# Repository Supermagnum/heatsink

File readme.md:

# DIY Liquid Cooling Suit

Those are cooling suits, used in the lowest layer on space suits.
It has hoses for circulation of cooling medium. 
A single layer of fabric may be used, with the tubing either on the inside directly contacting the wearer's skin, or on the outside separated by the fabric. If two layers of fabric are used, stitched channels can be formed which enclose the tubing between the two fabric layers. Where flame resistance is needed, the garment may be constructed out of materials such as nomex. 
If anyone has seen the apollo 13 movie, the boxes carried by the astronauts on the way to the space capsule is a heat exchanger that provides cooling until the suits can be hooked up to the capsules internal cooling system.
That box also provides O2.

I think that NASA just used ice, battery and a pump in those boxes, and you need the capacity to at least transport 200W because the human body generates about 100W. One could rip out the heat exchanger from a car, the bit who heats air, make the suit out of spandex and sew in loops. Mesh cloth or mesh garments are also suitable. 
A radiator for a CPU liquid cooler should be ideal. Hook that up to a aquarium pump or similar, and the heat exchanger/radiator that goes in a bucket of ice cubes or phase shifting material and water. The pump will need to be able to flow around 4 liters per minute, and must run on 12V and accept PWM control.

The cooling loop is made of 
6 pvc hoses in parallel, measuring 6 mm ØID x 9 mm ØOD, length 4 meters per hose. Total internal surface of the hoses is 4524.7 cm². External surface 6789.6 cm2. The heat exchanger as well as hoses and pump contain 3 liters of inhibited propylene glycol and water mix (25–30%). Brass or metal connectors, hose barbs, and hose clamps should be used. Two manifolds are required — one for liquid distribution and one for collection — built from T-pieces, elbows, and other fittings (see [Coolant plumbing](#coolant-plumbing) below).

## Table of contents

- [Thermal Calculations](#thermal-calculations)
  - [Cooling 3 liters from 40°C to 18°C](#cooling-3-liters-of-waterglycol-from-40c-to-18c-in-150-seconds)
  - [Ice as a cooling medium](#ice-as-a-cooling-medium)
  - [Maintaining 18°C coolant temperature](#maintaining-18c-coolant-temperature)
  - [Liquid-to-ice heat exchanger](#liquid-to-ice-heat-exchanger)
- [Phase-Change Materials](#phase-change-materials)
- [Temperature Control](#temperature-control)
  - [Coolant options](#coolant-options)
  - [Preliminary Arduino Firmware](#preliminary-arduino-firmware)
- [Required Hardware](#required-hardware)
- [Electronics component list](component-list.md)
  - [Assembly instructions](component-list.md#assembly-instructions)
  - [Board placement guide (arduino-shield.jpg)](component-list.md#board-placement-guide)
  - [Ordering the PCB from Gerber files](component-list.md#ordering-the-pcb-from-gerber-files)
  - [Soldering and wire splicing](component-list.md#soldering-and-wire-splicing)
  - [How to solder (NASA reference)](component-list.md#how-to-solder)
  - [How to splice wire properly](component-list.md#how-to-splice-wire-properly)
  - [Heat-shrink on splices](component-list.md#heat-shrink-on-splices)
- [Wiring Diagram](#wiring-diagram)
- [12V Power Setup](#12v-power-setup)
  - [12V DC safety and dry locations](#12v-dc-safety-and-dry-locations)
- [Container Setup](#container-setup)
- [Suit Fabric](#suit-fabric)
- [Coolant plumbing](#coolant-plumbing)
- [Pump Selection](#pump-selection)

---

## Thermal Calculations

### Cooling 3 liters of water/glycol from 40°C to 18°C in 150 seconds

How much heat must be removed:

Q = mc∆T  
m = 3 kg  
Specific heat capacity of water = 4.18 J/g°C  
Temperature change: 40 - 18 = 22°C

Q = 3 kg × 4180 J/kg°C × 22°C = **275,880 J**

This means the heat exchanger removes 275,880 joules of heat from the cooling loop in 150 seconds.

To convert joules into watts: Joules / time in seconds = **~1,848W** during initial cooldown.

---

### Ice as a cooling medium

To remove 1848.8 watts of energy from 3 liters of water at 40°C over 150 seconds:

Q = P × t = 1848.8 W × 150 s = **277,320 J**

Mass of water being cooled:

m = Q / (c × ΔT) = 277320 / (4.18 × 40) ≈ **1.658 kg**

So approximately 1.65 kilograms of ice would be needed for the initial cooldown phase.

It will take approximately 42.86 seconds to remove 275,880 joules of heat with a flow rate of 5 liters per minute.

---

### Maintaining 18°C coolant temperature

With ambient air temperature at 40°C:

ΔT_initial = 40°C - 18°C = 22°C

m_ice = (m × c × ΔT_initial) / L_f  
m_ice = (3 kg × 4186 J/kg°C × 22°C) / 334,000 J/kg ≈ **0.827 kg per hour**

Including 100W body heat: approximately **~2 kg of ice per hour** is needed.  
Flow rate for maintenance: **~2.5 liters per minute**.

---

### Liquid-to-ice heat exchanger

To extract 275,880 J of heat from ice over 150 seconds using 10mm OD / 0.8mm wall copper tube with a ΔT of 40°C and convective heat transfer coefficient of 200 W/m²·K:

Required copper tube length: approximately **7.32 meters**  
Inner surface: 1.848 m²  
Outer surface: 2.198 m²

---

## Phase-Change Materials

I suggest using Cold Gel Packs, Campingaz or similar brand as they reportedly last longer than ice cubes.

You can make something similar yourself:  
https://m.youtube.com/watch?v=Nqxjfp4Gi0k

- Heat capacity of the salt/water mixture: approximately **5,451.5 J/°C**
- Latent heat: approximately **3.39 J/g°C**
- Total weight of mixture: **1,695 grams**
- Be aware that it might expand slightly when frozen.
- Heat capacity of 1,695 grams of water ice: approximately **3,543.55 J/°C**

Also look at:  
https://www.cryopak.com/solutions/refrigerants/phase-change-materials/phase-5/

- Heat capacity of 2 kg mixture: approximately **6,432.92 J/°C**
- Heat capacity of 2 kg water ice: **4,180 J/°C**
- 2 kg of the mixture will last approximately **3 hours** — much better than water ice.

---

## Temperature Control

To keep coolant at 18°C (0°C coolant is uncomfortable and risks hypothermia):

Use an automotive NTC temperature sensor and an Arduino to control temperature. Sensor datasheet: [Bosch M12 NTC temperature sensor (PDF)](https://www.bosch-motorsport.com/content/downloads/Raceparts/Resources/pdf/Data%20sheet_70101387_Temperature_Sensor_NTC_M12.pdf)

Arduino shield schematic: [arduino-shield.pdf](arduino-shield/arduino-shield.pdf) ([shield project folder](arduino-shield/))

Mount the Bosch M12 NTC in the **collection manifold** (return side), as close to the suit as possible — **not in the ice container**. This measures warm coolant leaving the suit for pump control. Use PWM to regulate pump speed from that reading.

Why **inhibited propylene glycol** and water? The ice bath and phase-change blocks can drive slush **below 0°C** at the heat exchanger. A **25–30% PG mix** keeps the loop liquid while staying thin enough to pump through 6 mm hoses. Unlike ethylene glycol antifreeze, propylene glycol is **biodegradable and low-toxicity** — a better fit near a wearable loop (still not for drinking). Use secure hose barbs and clamps, pressure-test the loop, and increase PG percentage only if slush goes colder than your mix rating.

### Coolant options

#### Recommended — inhibited propylene glycol + water (25–30% mix)

**Best balance of cost, safety, and compatibility for this build.**

| Property | Detail |
| --- | --- |
| **Toxicity** | Non-toxic, food-grade safe. Used in RVs, food processing, and HVAC. Unlike ethylene glycol, PG is biodegradable and presents a much lower hazard to people and animals if spilled. |
| **Hose / seal compatibility** | Compatible with typical cooling-system plastics and elastomers — PVC hose, pump seals, and brass barbs used in this project. |
| **Freeze point** | ~**−10°C at 25%** PG — enough margin for light sub-zero slush without the extra viscosity and pumping cost of a 50% mix. Use **30%** if you need more headroom. |
| **Electrical** | **Not dielectric** — conductivity is typically **>2,000 µS/cm** (water-based, conductive). Fine for a pumped hose loop; do not use near bare electronics expecting insulation. |
| **Cost / availability** | Cheapest practical option. Sold as pre-mixed **inhibited** PG antifreeze under names such as **DOWFROST**, **AMSOIL ANT**, **Cryo-Tek**, or generic **RV / marine antifreeze** at hardware and auto stores. Confirm the label says **propylene glycol**, not ethylene glycol. |

Mix with **distilled water** if buying full-strength concentrate; follow the label for your target freeze point.

#### Optional — ElectroCool and similar synthetic fluids

**ElectroCool** (Engineered Fluids) and similar **dielectric** immersion coolants are non-conductive and wash off with soap and water, but they are **much more expensive** and designed for electronics immersion — not as a default for this PVC-hose suit loop. Only consider if you validate compatibility with every hose, pump seal, and fitting, and accept the higher fluid cost.

#### Other alternatives

| Fluid | Notes |
| --- | --- |
| **USP / food-grade PG + water (DIY mix)** | Same family as above; buy PG concentrate and mix yourself. Lowest unit cost. |
| **Glycerol (glycerin) + water** | Non-toxic and biodegradable. Higher viscosity — may reduce flow in 6 mm hoses; weaker freeze protection per percent than PG. |
| **Potassium acetate / formate HTF** | Used in some commercial low-toxicity antifreeze systems. Verify pump, hose, and brass compatibility before use. |

#### Not recommended for a wearable loop

- **Ethylene glycol** (standard automotive antifreeze) — effective antifreeze but **acutely toxic**
- **Legacy PFAS / fluorinated fluids** — environmental persistence and regulatory phase-out
- **Plain water** — inadequate when slush goes below 0°C at the heat exchanger

#### Fill and service

- Use **distilled water** for mixing; tap water minerals cause scale and biofilm
- Pressure-test after fill; monitor for leaks on first runs (see [Coolant plumbing](#coolant-plumbing))
- Label the container and suit loop as containing glycol — not potable

### Preliminary Arduino Firmware

Two **momentary** switches adjust coolant temperature between 15°C and 25°C in 5°C steps (up/down).  
A **maintained toggle** switch on D4 enables manual pump override (full PWM on D9); off returns to automatic temperature control.  
Outputs on the [Arduino shield](arduino-shield/arduino-shield.pdf):
- **D9 → Q1 (TIP120):** pump PWM (temperature-controlled, or manual override via D4)
- **D7:** buzzer — out-of-ice alarm (>30°C for 2 minutes)
- **D8 → Q2 (TIP120):** spare 12V output (not used in current firmware)

LCD shows: target temperature, sensed temperature, current pump PWM.

Firmware repository:  
https://github.com/Supermagnum/heatsink/tree/main/firmware

---

## Required Hardware

1. **Arduino Uno R3** — bottom of the stack; see [component list](component-list.md)
2. [Heatsink control shield](arduino-shield/arduino-shield.pdf) — stacks on the Uno; [placement diagram](arduino-shield/arduino-shield.jpg) shows part positions, diode direction, and **+** wire marks. Order bare PCBs from [`arduino-shield/gerbers/`](arduino-shield/gerbers/) ([how to submit Gerbers](component-list.md#ordering-the-pcb-from-gerber-files)), then follow [assembly instructions](component-list.md#assembly-instructions). New to soldering? **20 W iron** and NASA/splice guides in [component list — Soldering and wire splicing](component-list.md#soldering-and-wire-splicing)
3. **LCD shield, 20×4, no buttons** — HD44780 display-only shield on top of the stack (not an LCD Keypad Shield)
4. NTC thermistor, [Bosch M12](https://www.bosch-motorsport.com/content/downloads/Raceparts/Resources/pdf/Data%20sheet_70101387_Temperature_Sensor_NTC_M12.pdf) (see [Coolant plumbing](#coolant-plumbing) for mounting)
5. **R1** — **MFP50SBBE52-50K** (50 kΩ, 0.1%) — DigiKey **MFP50SBBE52-50K-ND**
6. **D1–D3** — three **1N5407RL** flyback diodes — DigiKey **1N5407RL-ND** (or **1N5407RLG-ND** if unavailable)
7. **2× M3 nylon bolt and nut** — mount **Q1** and **Q2** tabs only; **no metal** hardware (12 V)
8. Shield stacking headers — DigiKey **1528-1074-ND** (Adafruit #85), one kit per bare control shield for Uno/LCD stack ([full DigiKey list](component-list.md#digikey-quick-order-bare-shield-populate))
9. Three **panel switches** on **SW1–SW3** (1×3 headers): two **100SP4T1B2M2QE** momentary (temp up/down), one **ANT13SECQE** maintained toggle (pump manual/auto). **Switch guards** (100SP / ANT compatible) recommended to prevent accidental actuation — especially on SW3
10. 12V submersible pump (4–5 L/min) — switched by **Q1 TIP120 on D9** on the control shield (max **5A**)
11. Optional: **5A inline fuses** on each 12V power cable branch (see [12V Power Setup](#12v-power-setup))
12. Crimped leads / screw terminals for panel switches, NTC, and 12 V — see [component list](component-list.md)
13. Hose clamps
14. Assorted T-pieces, elbows, connectors, adapters, and tube barbs (metal or PETG — see [Coolant plumbing](#coolant-plumbing))
15. Inhibited propylene glycol antifreeze (propylene, not ethylene) for 25–30% coolant mix
16. Liquid gasket or PTFE thread tape for sealed joints
17. Optional: small valves to control "zones"

### Arduino stack and connections

**Stack (bottom → top):** Arduino Uno R3 → heatsink control shield → **LCD shield without buttons**. Panel switches and NTC connect to the control shield headers/terminals only.

- Bosch M12 NTC (TH1) and 50K resistor (R1) form a voltage divider on A0; AREF feeds the divider top and sets the ADC reference
- **LCD shield** (20×4, HD44780, **no keypad**) on D12, D11, D10, D6, D5, D13 — see [Wiring Diagram](#wiring-diagram)
- Switches wired **pin → switch → GND** (active when grounded); firmware enables internal pull-ups on D2, D3, and D4
- **D2 / D3:** momentary — one temperature step per actuation
- **D4:** maintained toggle — ON = manual pump override, OFF = automatic
- D9 PWM drives **Q1 TIP120** on the shield — low-side switch for the pump (up to 5A)
- D7 drives the **buzzer** alarm output
- D8 drives **Q2 TIP120** for the spare 12V output
- Q1 and Q2 are TO-220 packages clamped to **built-in copper thermal zones** with **M3 nylon bolt and nut** each — **no metal mounting hardware** (12 V on the tab). **No add-on heatsinks**; the PCB spreads heat from the transistor tabs

---

## Wiring Diagram

Signal and power connections for the [Arduino shield](arduino-shield/arduino-shield.pdf). Ground all 12V loads to a common bus.

```mermaid
graph TD
    PSU["12V PSU / Battery"]

    PSU -->|12V| ARD["Arduino Uno\n+ control shield"]
    PSU -->|12V| Q1["TIP120 Q1\npump D9"]
    PSU -->|12V| Q2["TIP120 Q2\nspare D8"]

    ARD -->|D9 PWM| Q1
    Q1 --> PUMP["Submersible pump\n4–5 L/min"]

    ARD -->|D7| BUZ["Buzzer\nout-of-ice alarm"]
    ARD -->|D8| Q2
    Q2 --> SPARE["Spare 12V load\n(no firmware control)"]

    AREF["AREF-voltage"] -->|divider top + ADC ref| ARD
    AREF --> R1["R1 50K"]
    R1 -->|Vsense A0| ARD
    R1 --- TH1["TH1 Bosch M12 NTC\ncollection manifold\nat suit"]
    TH1 --> GND["Common GND"]

    SW1["SW1 Temp up\nmomentary"] -->|D2 — GND when closed| ARD
    SW2["SW2 Temp down\nmomentary"] -->|D3 — GND when closed| ARD
    SW3["SW3 Pump override\nmaintained toggle"] -->|D4 — GND when ON| ARD

    LCD["LCD 20x4"] -->|D12 RS, D11 E, D10 D4\nD6 D5, D13 D7| ARD

    ARD --- GND
    Q1 --- GND
    Q2 --- GND
    PUMP --- GND
    PSU --- GND
```

### Pin summary

| Pin | Function |
| --- | --- |
| A0 | NTC sense (R1 / TH1 junction) |
| AREF | Divider reference (same rail as R1 top) |
| D2 | SW1 momentary — target temperature up (+5°C per actuation) |
| D3 | SW2 momentary — target temperature down (−5°C per actuation) |
| D4 | SW3 maintained toggle — manual pump override (ON = full PWM) |
| D7 | Buzzer alarm (auto, >30°C for 2 min) |
| D8 | Q2 spare 12V output |
| D9 | Pump PWM via Q1 TIP120 |
| D5, D6, D10–D13 | LCD data and control |

**Switch wiring:** Panel switches **100SP4T1B2M2QE** (SW1, SW2) and **ANT13SECQE** (SW3) connect via **SW1–SW3** headers: **pin → switch → GND**. Internal pull-ups are enabled in firmware (`INPUT_PULLUP`); closed / ON = LOW. Add **switch guards** (100SP / ANT series) on the panel to reduce accidental toggles — especially on the pump override (SW3).

**NTC placement:** TH1 threads into the **collection manifold** on the return path, positioned **as close to the suit as practical** — not in the insulated container. The sensor cable runs back to the Arduino shield.

**NTC divider:** `AREF-voltage — R1 (50K) — A0 — TH1 (Bosch M12) — GND`. Firmware calls `analogReference(EXTERNAL)` so ADC readings match the divider supply.

**Pump override (SW3 / D4):** Maintained toggle — **ON** = full pump PWM via Q1; **OFF** = automatic temperature control.

**Temp switches (SW1 / SW2):** Momentary — one ±5°C step per actuation (debounced).

**12V loads:** Pump current flows through **Q1** on the shield — not through Arduino I/O pins directly. Q2 switches the spare load. D7 drives the buzzer. Add a **5A inline fuse** on each 12V feed (Arduino, pump/Q1, Q2) if not already fused at the battery.

---

## 12V Power Setup

```mermaid
graph LR
    BAT["12V Battery\nor PSU"]

    BAT --> FUSE_MAIN["Fuse 5A max\n(battery lead)"]
    FUSE_MAIN --> BUS["12V Distribution Bus"]

    BUS --> FUSE_A["Fuse 5A"] --> ARD["Arduino + LCD\n(~1A max)"]
    BUS --> FUSE_B["Fuse 5A"] --> PUMP_RAIL["Q1 pump rail\n(up to 5A)"]
    BUS --> FUSE_C["Fuse 5A"] --> Q2_RAIL["Q2 spare output"]

    GND["Common Ground Bus"] --- ARD
    GND --- PUMP_RAIL
    GND --- Q2_RAIL
    GND --- BAT
```

**Notes:**
- All components share a common ground
- Use **5A inline fuses maximum** on each 12V power cable branch (battery lead plus Arduino, pump/Q1, and Q2 feeds). Do not exceed 5A fuse rating on these cables
- The Arduino can be powered directly from 12V via its barrel jack (onboard regulator handles 5V/3.3V internally)
- The pump is switched by **Q1 TIP120 on the control shield** (D9 PWM) — do not connect pump current through Arduino pins
- Q1 and Q2 are rated up to 5A; size the pump accordingly
- Use appropriately rated wire gauge: 1.5mm² minimum for pump circuit, 0.5mm² for signal wiring
- TIP120 transistors (Q1, Q2) mount to **copper thermal zones** on the shield PCB with **M3 nylon** bolt and nut — **do not use metal** fasteners at the tabs; no separate heatsinks needed

**Battery sizing (portable use):**
- Pump draw: approximately 3-5A at 12V = 36-60W (Q1 TIP120 and pump fuse at **5A max**)
- Arduino + transistors + LCD: approximately 0.3A = 4W
- Total: approximately 4-5A continuous with a 5A fuse on the pump feed at the upper limit — avoid sustained overload
- A 20Ah 12V LiFePO4 battery gives approximately 3-4 hours runtime, matching the phase-change block duration

### 12V DC safety and dry locations

12 V is low enough that it is not mains shock hazard, but this system can still draw **several amps continuously**. Treat wiring like any other DC power installation: fused, correct gauge, and kept away from coolant and condensation.

**Electrical safety (12 V DC):**

- **Fuse every branch** at **5 A maximum** (battery lead plus Arduino, pump/Q1, and Q2). Fuses protect wire and battery from shorts — not optional.
- **Wire gauge:** **1.5 mm² minimum** on pump and battery feeds; **0.5 mm²** for signals. Undersized wire heats up under 3–5 A load.
- **Polarity:** Double-check **+12 V and GND** before connecting the battery. Reverse polarity can destroy the Arduino, shield, and pump controller.
- **One common ground** for battery, Arduino stack, pump return, and Q1/Q2 switching. Do not rely on the suit or frame as a ground path.
- **Pump current through Q1 only** — never through Arduino pins. The TIP120 switches the low side; the pump (+) comes from the fused 12 V bus.
- **Q1 / Q2 tab fasteners:** **M3 nylon** bolt and nut only — **no metal** at the transistor tabs (live **12 V**).
- **De-energize for wiring** — disconnect the battery or remove fuses when crimping, moving terminals, or opening the control enclosure.
- **Strain relief and insulation** — no bare copper at the panel or inside the box; use screw terminals or crimps where possible. **Every soldered splice must be covered with heat-shrink** (the [splice reference video](component-list.md#soldering-and-wire-splicing) does not show this step). Tie down cables so connectors are not pulled loose in use.
- **Coolant is conductive** — a glycol leak onto bare 12 V terminals can cause shorts, heating, or fire. Keep splices out of drip paths; wipe spills before re-energizing.
- **Batteries:** Use a proper 12 V pack (e.g. LiFePO4) with a BMS or charger matched to the chemistry. Do not short the terminals; store and charge in a dry, ventilated area away from flammable material.

**Keep dry — control unit and related electronics:**

Mount the **control unit** in a **dry enclosure** outside the ice container. It consists of:

| Keep dry | Location |
| --- | --- |
| **Arduino Uno R3 + heatsink control shield + LCD shield** (stacked) | Inside a sealed project box or small case on the suit harness, belt, or backpack — **not** in the cooler |
| **12 V battery** (if portable) | Same dry area as the control unit; protect from sweat, rain, and spills |
| **Panel switches** (SW1–SW3) | On the operator panel; guards help mechanically — use splash-aware routing if exposed |
| **NTC cable (TH1)** | Sensor threads into the **wet** manifold; only the **M12 sensor tip** sees coolant. The cable and connector back to the shield must stay **dry** — route upward from the manifold and seal the panel penetration |

**Allowed to get wet (by design):**

| Wet location | Parts |
| --- | --- |
| **Inside the insulated cooler** | Submersible pump, radiator, ice/slush, coolant hoses through the lid |
| **Suit loop** | PVC hoses, manifolds, fittings, and the Bosch M12 sensing element in the collection manifold |

Only **12 V pump power** and **coolant hoses** should pass through the cooler lid (grommeted or sealed). Run signal and Arduino power from the **dry control box** — do not submerge the stack, battery, or unsealed junctions. If the enclosure may see humidity, use vented or IP-rated boxes and keep connectors inside the lid line.

See also [Container Setup](#container-setup) for lid penetrations and [component list](component-list.md) for stack parts.

---

## Container Setup

```mermaid
graph TD
    LID["Insulated Cooler Lid\n(15-20 litre cooler)"]

    LID -->|Sealed penetrations| HOSE_IN["Coolant hose IN\n(warm return from suit)"]
    LID -->|Sealed penetrations| HOSE_OUT["Coolant hose OUT\n(chilled supply to suit)"]
    LID -->|Sealed penetrations| POWER["12V power cable\n(to pump)"]

    subgraph CONTAINER["Insulated Container (interior)"]
        RAD["240mm PC Radiator\n(submerged, bottom-mounted)"]
        PUMP_S["Submersible Pump\n(brushless 12V DC)"]
        ICE["Ice / Phase-Change Blocks\n(~2kg per hour runtime)"]
        WATER["Water filling gaps\nfor thermal contact"]
        RAD --- ICE
        PUMP_S --- ICE
        ICE --- WATER
    end

    HOSE_IN -->|warm coolant from suit| RAD
    RAD -->|cooled coolant| PUMP_S
    PUMP_S -->|cooled coolant| HOSE_OUT
```

**Container notes:**
- Use a quality foam-insulated cooler (camping/outdoor grade) with a good lid seal
- The radiator sits at the bottom, fully submerged in ice water — this gives 5-10× better heat transfer than air cooling
- The submersible pump also sits inside the container, drawing chilled water/glycol
- All lid penetrations (hoses and **pump 12 V power only**) should be sealed with silicone or grommets to prevent warm air ingress and leaks
- The **Arduino control unit** (stack, battery, dry wiring) stays **outside** the cooler — see [12V DC safety and dry locations](#12v-dc-safety-and-dry-locations)
- Fill gaps around ice/phase-change blocks with water to maximise thermal contact with the radiator
- The NTC sensor is **not** mounted in the container — it sits in the **collection manifold at the suit** (see [Coolant plumbing](#coolant-plumbing))

**Radiator sizing:**
- A 240mm radiator (air-rated ~300W) performs at approximately 1,500-3,000W when submerged in ice water
- This comfortably covers the 1,848W initial cooldown load and the 100W maintenance load
- A 360mm radiator provides additional headroom, particularly useful with phase-change blocks which have less uniform surface contact than liquid ice water

---

## Suit Fabric

**Recommended: Cotton mesh**

Cotton mesh is the best choice for this application because:
- Breathable open weave allows direct skin contact with the cooling tubes
- Cotton is comfortable and non-irritating against skin during extended wear
- Natural fibre — does not trap heat against the body
- Easy to sew channels or loops for routing the 6mm/9mm PVC hoses
- Washable and durable

**Construction:**
- Sew hose channels directly into the mesh using a zigzag or channel stitch
- Route hoses in parallel loops across the torso, back, and limbs as needed
- Connect the six suit hoses to distribution and collection manifolds (see [Coolant plumbing](#coolant-plumbing))
- Optional zone valves allow sections of the suit to be isolated, reducing flow to areas not needed

---

## Coolant plumbing

Two manifolds are needed: one splits flow from the supply line into the six parallel suit hoses, and one merges the return lines back toward the heat exchanger.

**NTC sensor placement:**
- Install the Bosch M12 sensor (TH1) in the **collection manifold** — the return manifold where warmed coolant from the suit hoses combines
- Place the port **as close to the suit as possible**, before the long hose run back to the container
- The sensor measures coolant temperature **leaving the suit**, which is what the Arduino uses for pump control — not the chilled fluid inside the ice box

**Fittings:**
- Several T-pieces, elbows, and connectors sized for 6 mm ID / 9 mm OD hose
- Metal (brass) barbs and fittings are the most durable option
- Manifolds can alternatively be **3D printed in PETG** if wall thickness and infill are high enough for pressure (typically 40% infill or higher, with solid perimeters around barb ports)

**Bosch M12 sensor mounting (metal route):**
- A suitable **drill and M12 tap** are required to thread the port for the Bosch M12 sensor
- Seal threads with **liquid gasket** or **PTFE tape**

**Assembly and testing:**
- Use liquid gasket or PTFE tape on all threaded connections
- **Pressure-test** the completed loop before use and **monitor for leaks** during initial runs
- Fix any weeping joints before relying on the system in service
- Electronics build and bench test: [assembly instructions](component-list.md#assembly-instructions) (Steps 5–6)

---

## Pump Selection

**Requirements:**
- 12V DC brushless, submersible rated
- Flow rate: 4-5 liters/minute (minimum)
- Continuous duty rated
- PWM controllable (dedicated PWM signal wire preferred)
- ½ inch inlet and outlet
- Compatible with inhibited propylene glycol and water mix (25–30%)

**Search terms:**
- "12V DC brushless submersible pump PWM 5LPM"
- "12V DC pump 300LPH PWM control"

Check aquarium suppliers, solar pump suppliers, and irrigation suppliers. Gear and diaphragm pumps handle PWM better than centrifugal types at this flow rate. Centrifugal pumps require priming and cannot be controlled as precisely.

**PWM control note:** The shield uses **Q1 TIP120** on D9 for low-side PWM of the pump. Many brushless pumps tolerate slow PWM on the power side; if the pump stutters, try a pump with a dedicated PWM input wire or add a smoothing capacitor on the pump supply. Stay within the **5A** Q1 and fuse limit.

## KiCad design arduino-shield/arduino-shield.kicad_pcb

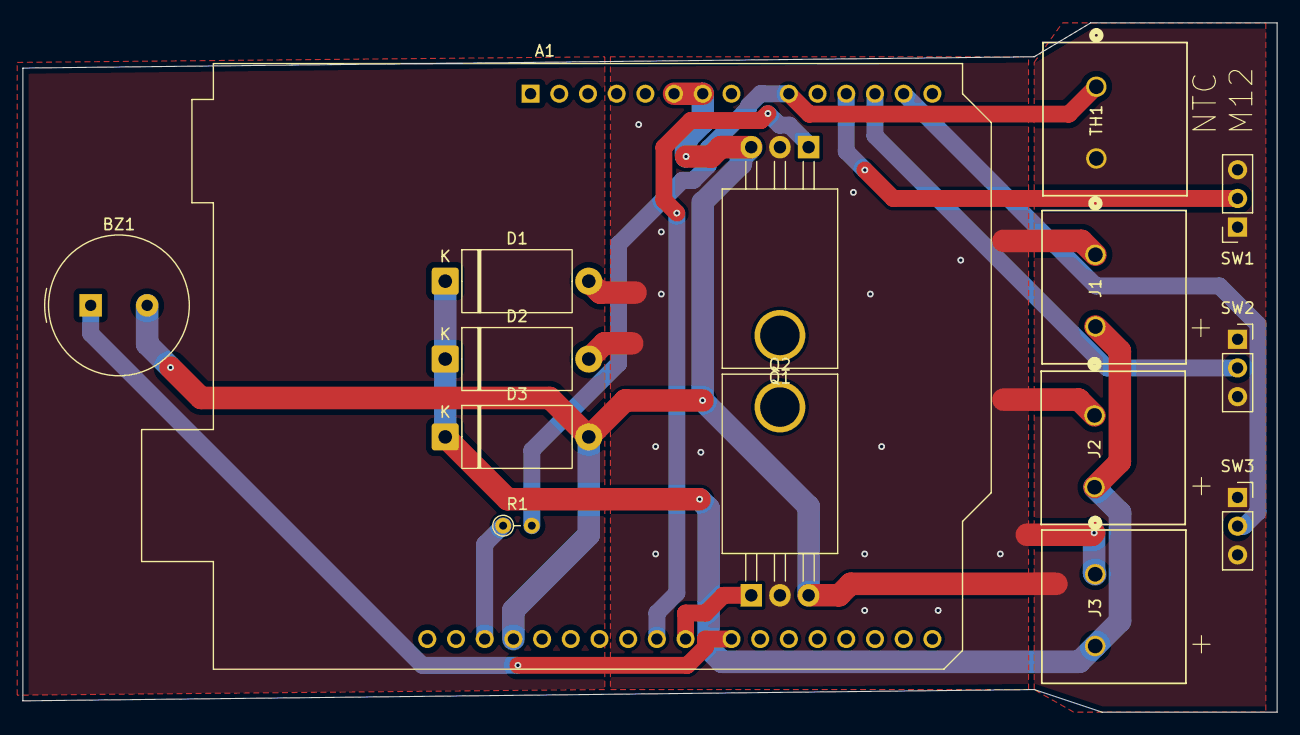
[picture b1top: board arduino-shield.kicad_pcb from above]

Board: 2 copper layers, 111.0 x 61.0 mm, 15 parts (0 on the bottom side), 11 nets.

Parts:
A1: Arduino_UNO_R3; Arduino_UNO_R3_
BZ1: Buzzer; Buzzer_TDK_PS1240P02BT_D12.2mm_H6.5mm
D1, D2, D3: 1N5407RL; D_DO-27_P12.70mm_Horizontal
J1, J2, J3: 393800102; CONN2_0393800102_524X492_MOL
Q1, Q2: TIP120; TO-220-3_Horizontal_TabDown
R1: 50K; R_Axial_DIN0204_L3.6mm_D1.6mm_P2.54mm_Vertical
SW1, SW2: 100SP4T1B2M2QE; PinSocket_1x03_P2.54mm_Vertical
SW3: ANT13SECQE; PinSocket_1x03_P2.54mm_Vertical
TH1: Thermistor_NTC_ Bosch M12; CONN2_0393800102_524X492_MOL

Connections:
12vdc: D1.1 (K), D2.1 (K), D3.1 (K), J1.2, J2.2, J3.2
/current: D1.2 (A), D2.2 (A), J1.1, J2.1, J3.1, Q1.2 (C), Q2.2 (C)
AREF-voltage: A1.30 (AREF), R1.1
GND: A1.6 (GND), A1.7 (GND), A1.29 (GND), BZ1.2 (-), D3.2 (A), Q1.3 (E), Q2.3 (E), SW1.1 (A), SW1.3 (C), SW2.1 (C), SW2.3 (A), SW3.1 (A), SW3.3 (C), TH1.2
Vsense: A1.9 (A0), R1.2, TH1.1
buzzer+: A1.22 (D7), BZ1.1 (+)
pump-pwm: A1.24 (D9), Q1.1 (B)
relay2pin: A1.23 (D8), Q2.1 (B)
relay_control: A1.13 (A4), SW3.2 (B)
temp_down: A1.12 (A3), SW2.2 (B)
temp_up: A1.11 (A2), SW1.2 (B)

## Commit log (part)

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2023-08-16 Update readme.txt
    Update with maths to solve for ambient temperature.
2026-05-14 Update reference link in README
2026-05-24 Revise readme for clarity and organization
    Updated the readme to enhance clarity and structure, added sections for thermal calculations, required hardware, and pump selection, and improved formatting for better readability.
2026-05-24 Refactor pump control code and improve readability
